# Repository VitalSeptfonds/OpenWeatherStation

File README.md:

# OpenWeatherStation

## The Project
The main goal is to create an Open Weather Station based on STM32.
This weather station will give access to real time data through an Web API.

### Main Functionality 
- POE : Power Over Ethernet
- 3D printable 
- Ingress Protection : IP33
  - Protected from tools and wires greater than 2.5 millimeters
  - Protected from water spray less than 60 degrees from vertical
- Real time data
- Sensors :
  - Temperature
  - Humidity
  - Pressure
  - Light

## API
### Request
`GET /get_data/`

Return Real Time Data

### Response

    {
      "time" : "01/01/01 00:00:00",
      "data" :
        {
          "temperature" : 20.00,
          "humidity" : 50,
          "pressure" : 1013,
          "light" : 3000
        }

    }

## Error handling

Error responses should include a common HTTP status code, message for the developer, message for the end-user (when appropriate), internal error code

    {
      "error" :
        {
          "status" : 400,
          "errorCode" : "444444",
          "errorMessage" : "Verbose, plain language description of the problem. Provide developers
           suggestions about how to solve their problems here",
          "userMessage" : "This is a message that can be passed along to end-users, if needed."
         }
    }

Use three simple, common response codes :

* 400 - Bad Request
* 404 - Not Found
* 500 - Internal Server Error

## Links
* [Hardware](hardware/readme.md)
* [Software](software/readme.md)

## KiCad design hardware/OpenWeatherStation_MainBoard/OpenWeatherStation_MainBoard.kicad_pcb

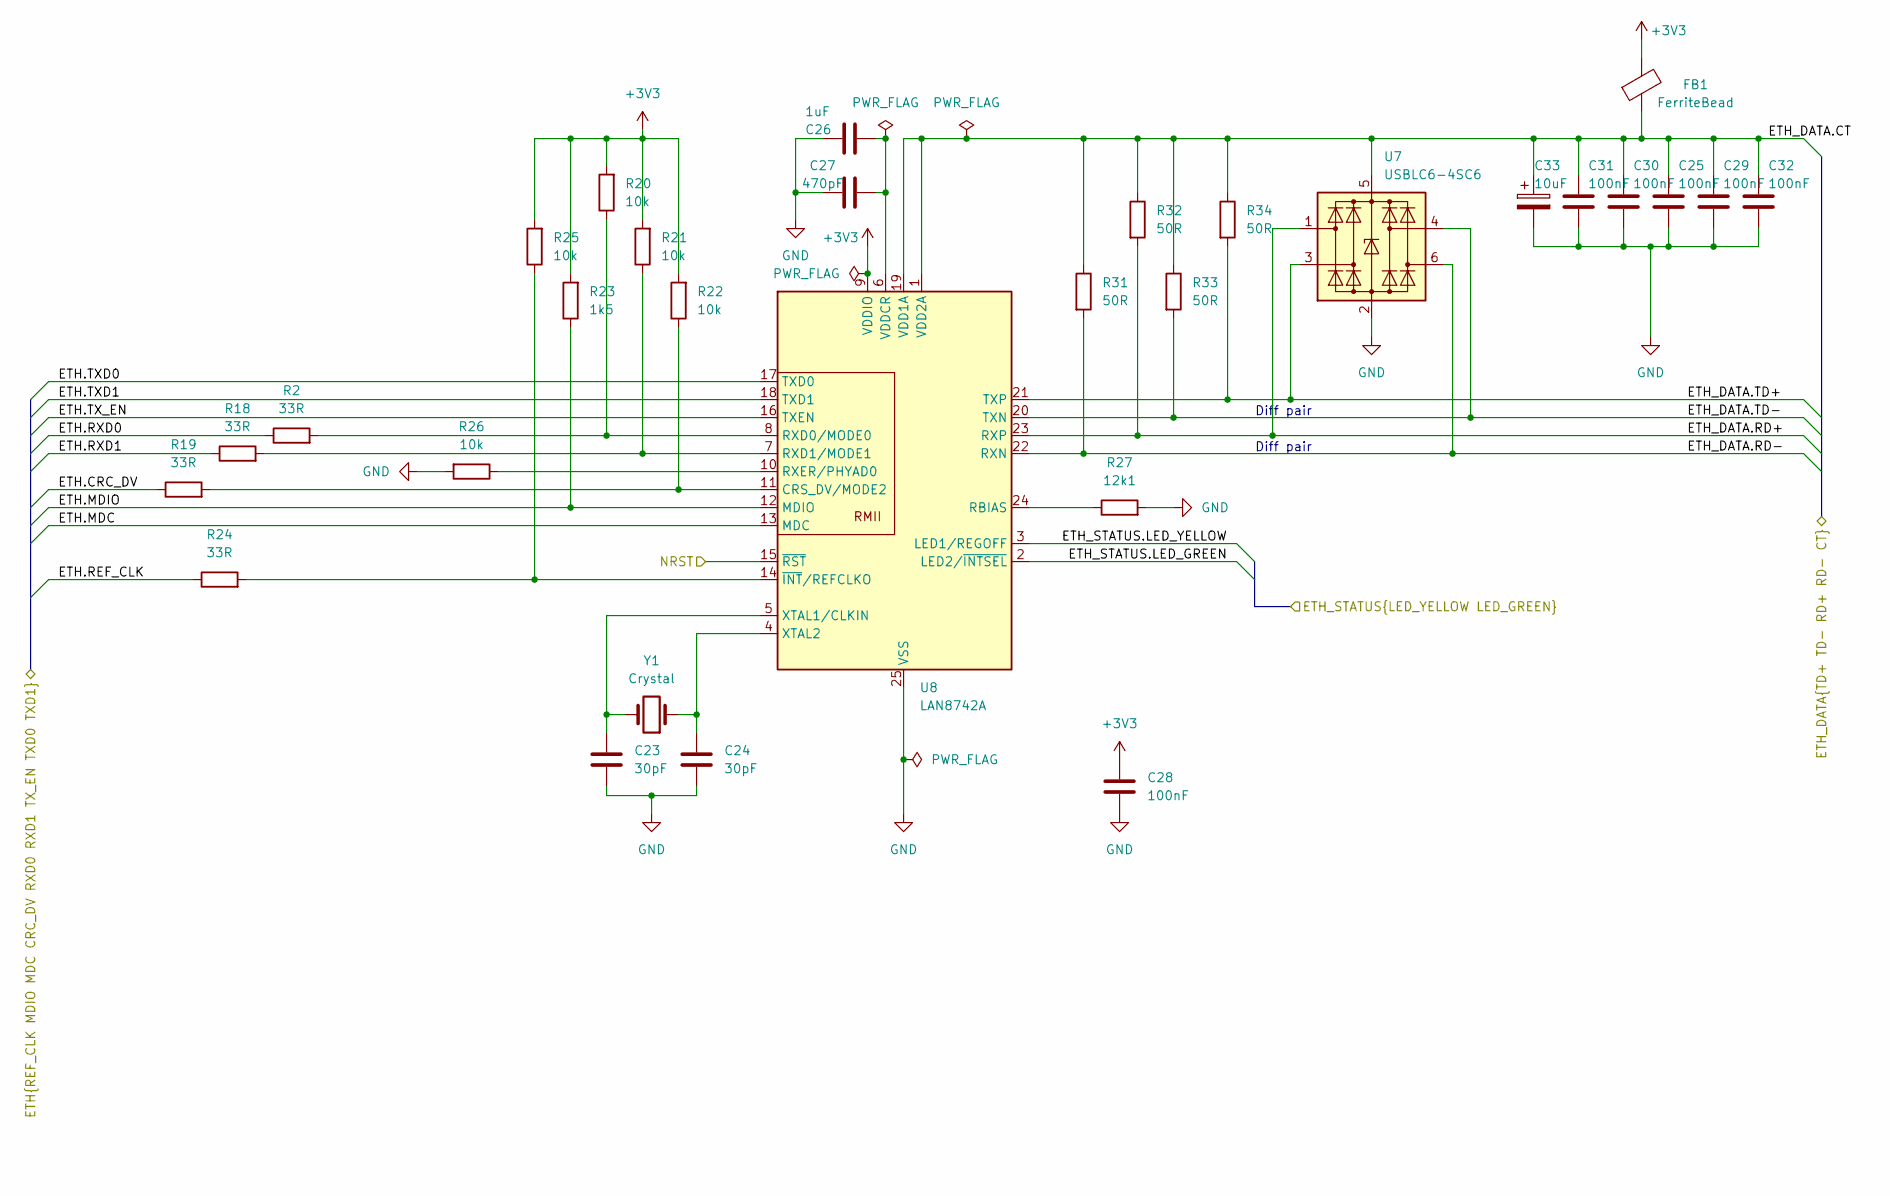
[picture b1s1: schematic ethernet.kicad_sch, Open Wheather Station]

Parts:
C23, C24: 30pF; C_0603_1608Metric
C25, C28, C29, C30, C31, C32: 100nF; C_0603_1608Metric
C26: 1uF; C_0603_1608Metric
C27: 470pF; C_0603_1608Metric
C33: 10uF; C_0603_1608Metric
FB1: FerriteBead; C_0603_1608Metric
R2, R18, R19, R24: 33R; R_0603_1608Metric
R20, R21, R22, R25, R26: 10k; R_0603_1608Metric
R23: 1k5; R_0603_1608Metric
R27: 12k1; R_0603_1608Metric
R31, R32, R33, R34: 50R; R_0603_1608Metric
U7: USBLC6-4SC6; SOT-23-6
U8: LAN8742A; VQFN-24-1EP_4x4mm_P0.5mm_EP2.5x2.5mm_ThermalVias
Y1: Crystal; Crystal_SMD_Abracon_ABM3B-4Pin_5.0x3.2mm

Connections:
+3V3: C28.1, FB1.2, R20.2, R21.2, R22.2, R23.2, R25.2, U8.9 (VDDIO); also elsewhere on the board
/Connectors/ETH_STATUS.LED_GREEN: U8.2 (LED2/~INTSEL); also elsewhere on the board
/Connectors/ETH_STATUS.LED_YELLOW: U8.3 (LED1/REGOFF); also elsewhere on the board
/Connectors/NRST: U8.15 (~RST); also elsewhere on the board
/Ethernet/ETH.CRC_DV: R19.1; also elsewhere on the board
/Ethernet/ETH.MDC: U8.13 (MDC); also elsewhere on the board
/Ethernet/ETH.MDIO: R23.1, U8.12 (MDIO); also elsewhere on the board
/Ethernet/ETH.REF_CLK: R24.1; also elsewhere on the board
/Ethernet/ETH.RXD0: R2.1; also elsewhere on the board
/Ethernet/ETH.RXD1: R18.1; also elsewhere on the board
/Ethernet/ETH.TXD0: U8.17 (TXD0); also elsewhere on the board
/Ethernet/ETH.TXD1: U8.18 (TXD1); also elsewhere on the board
/Ethernet/ETH.TX_EN: U8.16 (TXEN); also elsewhere on the board
/Ethernet/ETH_DATA.CT: C25.1, C29.1, C30.1, C31.1, C32.1, C33.1, FB1.1, R31.1, R32.1, R33.1, R34.1, U7.5 (VBUS), U8.1 (VDD2A), U8.19 (VDD1A); also elsewhere on the board
/Ethernet/ETH_DATA.RD+: R32.2, U7.1 (I/O1), U8.23 (RXP); also elsewhere on the board
/Ethernet/ETH_DATA.RD-: R31.2, U7.6 (I/O4), U8.22 (RXN); also elsewhere on the board
/Ethernet/ETH_DATA.TD+: R34.2, U7.3 (I/O2), U8.21 (TXP); also elsewhere on the board
/Ethernet/ETH_DATA.TD-: R33.2, U7.4 (I/O3), U8.20 (TXN); also elsewhere on the board
GND: C23.2, C24.2, C25.2, C26.2, C27.1, C28.2, C29.2, C30.2, C31.2, C32.2, C33.2, R26.2, R27.2, U7.2 (GND), U8.25 (VSS); also elsewhere on the board
unnamed: R19.2, R22.1, U8.11 (CRS_DV/MODE2)
unnamed: R27.1, U8.24 (RBIAS)
unnamed: R2.2, R20.1, U8.8 (RXD0/MODE0)
unnamed: R18.2, R21.1, U8.7 (RXD1/MODE1)
unnamed: R26.1, U8.10 (RXER/PHYAD0)
unnamed: C26.1, C27.2, U8.6 (VDDCR)
unnamed: C23.1, U8.5 (XTAL1/CLKIN), Y1.2
unnamed: C24.1, U8.4 (XTAL2), Y1.1
unnamed: R24.2, R25.1, U8.14 (~INT/REFCLKO)

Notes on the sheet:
Diff pair

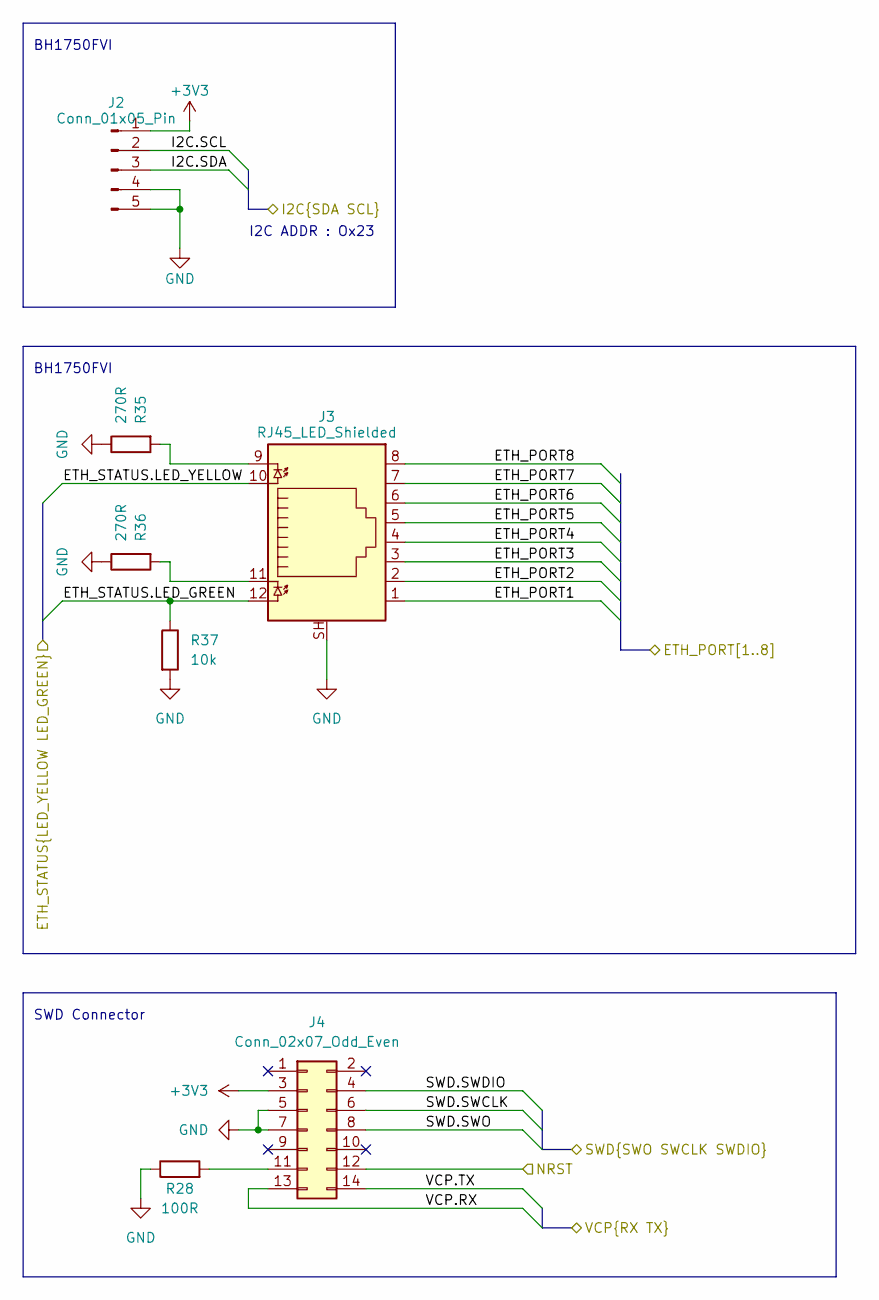
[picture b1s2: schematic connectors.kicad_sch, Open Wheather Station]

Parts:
J2: Conn_01x05_Pin; JST_XH_B5B-XH-A_1x05_P2.50mm_Vertical
J3: RJ45_LED_Shielded; RJ45_Amphenol_RJHSE538X
J4: Conn_02x07_Odd_Even; PinHeader_2x07_P1.27mm_Vertical
R28: 100R; R_0603_1608Metric
R35, R36: 270R; R_0603_1608Metric
R37: 10k; R_0603_1608Metric

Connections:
+3V3: J2.1, J4.3; also elsewhere on the board
/Connectors/ETH_PORT1: J3.1; also elsewhere on the board
/Connectors/ETH_PORT2: J3.2; also elsewhere on the board
/Connectors/ETH_PORT3: J3.3; also elsewhere on the board
/Connectors/ETH_PORT4: J3.4; also elsewhere on the board
/Connectors/ETH_PORT5: J3.5; also elsewhere on the board
/Connectors/ETH_PORT6: J3.6; also elsewhere on the board
/Connectors/ETH_PORT7: J3.7; also elsewhere on the board
/Connectors/ETH_PORT8: J3.8; also elsewhere on the board
/Connectors/ETH_STATUS.LED_GREEN: J3.12, R37.1; also elsewhere on the board
/Connectors/ETH_STATUS.LED_YELLOW: J3.10; also elsewhere on the board
/Connectors/I2C.SCL: J2.2; also elsewhere on the board
/Connectors/I2C.SDA: J2.3; also elsewhere on the board
/Connectors/NRST: J4.12; also elsewhere on the board
/Connectors/SWD.SWCLK: J4.6; also elsewhere on the board
/Connectors/SWD.SWDIO: J4.4; also elsewhere on the board
/Connectors/SWD.SWO: J4.8; also elsewhere on the board
/Connectors/VCP.RX: J4.13; also elsewhere on the board
/Connectors/VCP.TX: J4.14; also elsewhere on the board
GND: J2.4, J2.5, J3.SH, J4.5, J4.7, R28.1, R35.1, R36.1, R37.2; also elsewhere on the board
unnamed: J3.9, R35.2
unnamed: J3.11, R36.2
unnamed: J4.11, R28.2

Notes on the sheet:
SWD Connector
I2C ADDR : Ox23
BH1750FVI

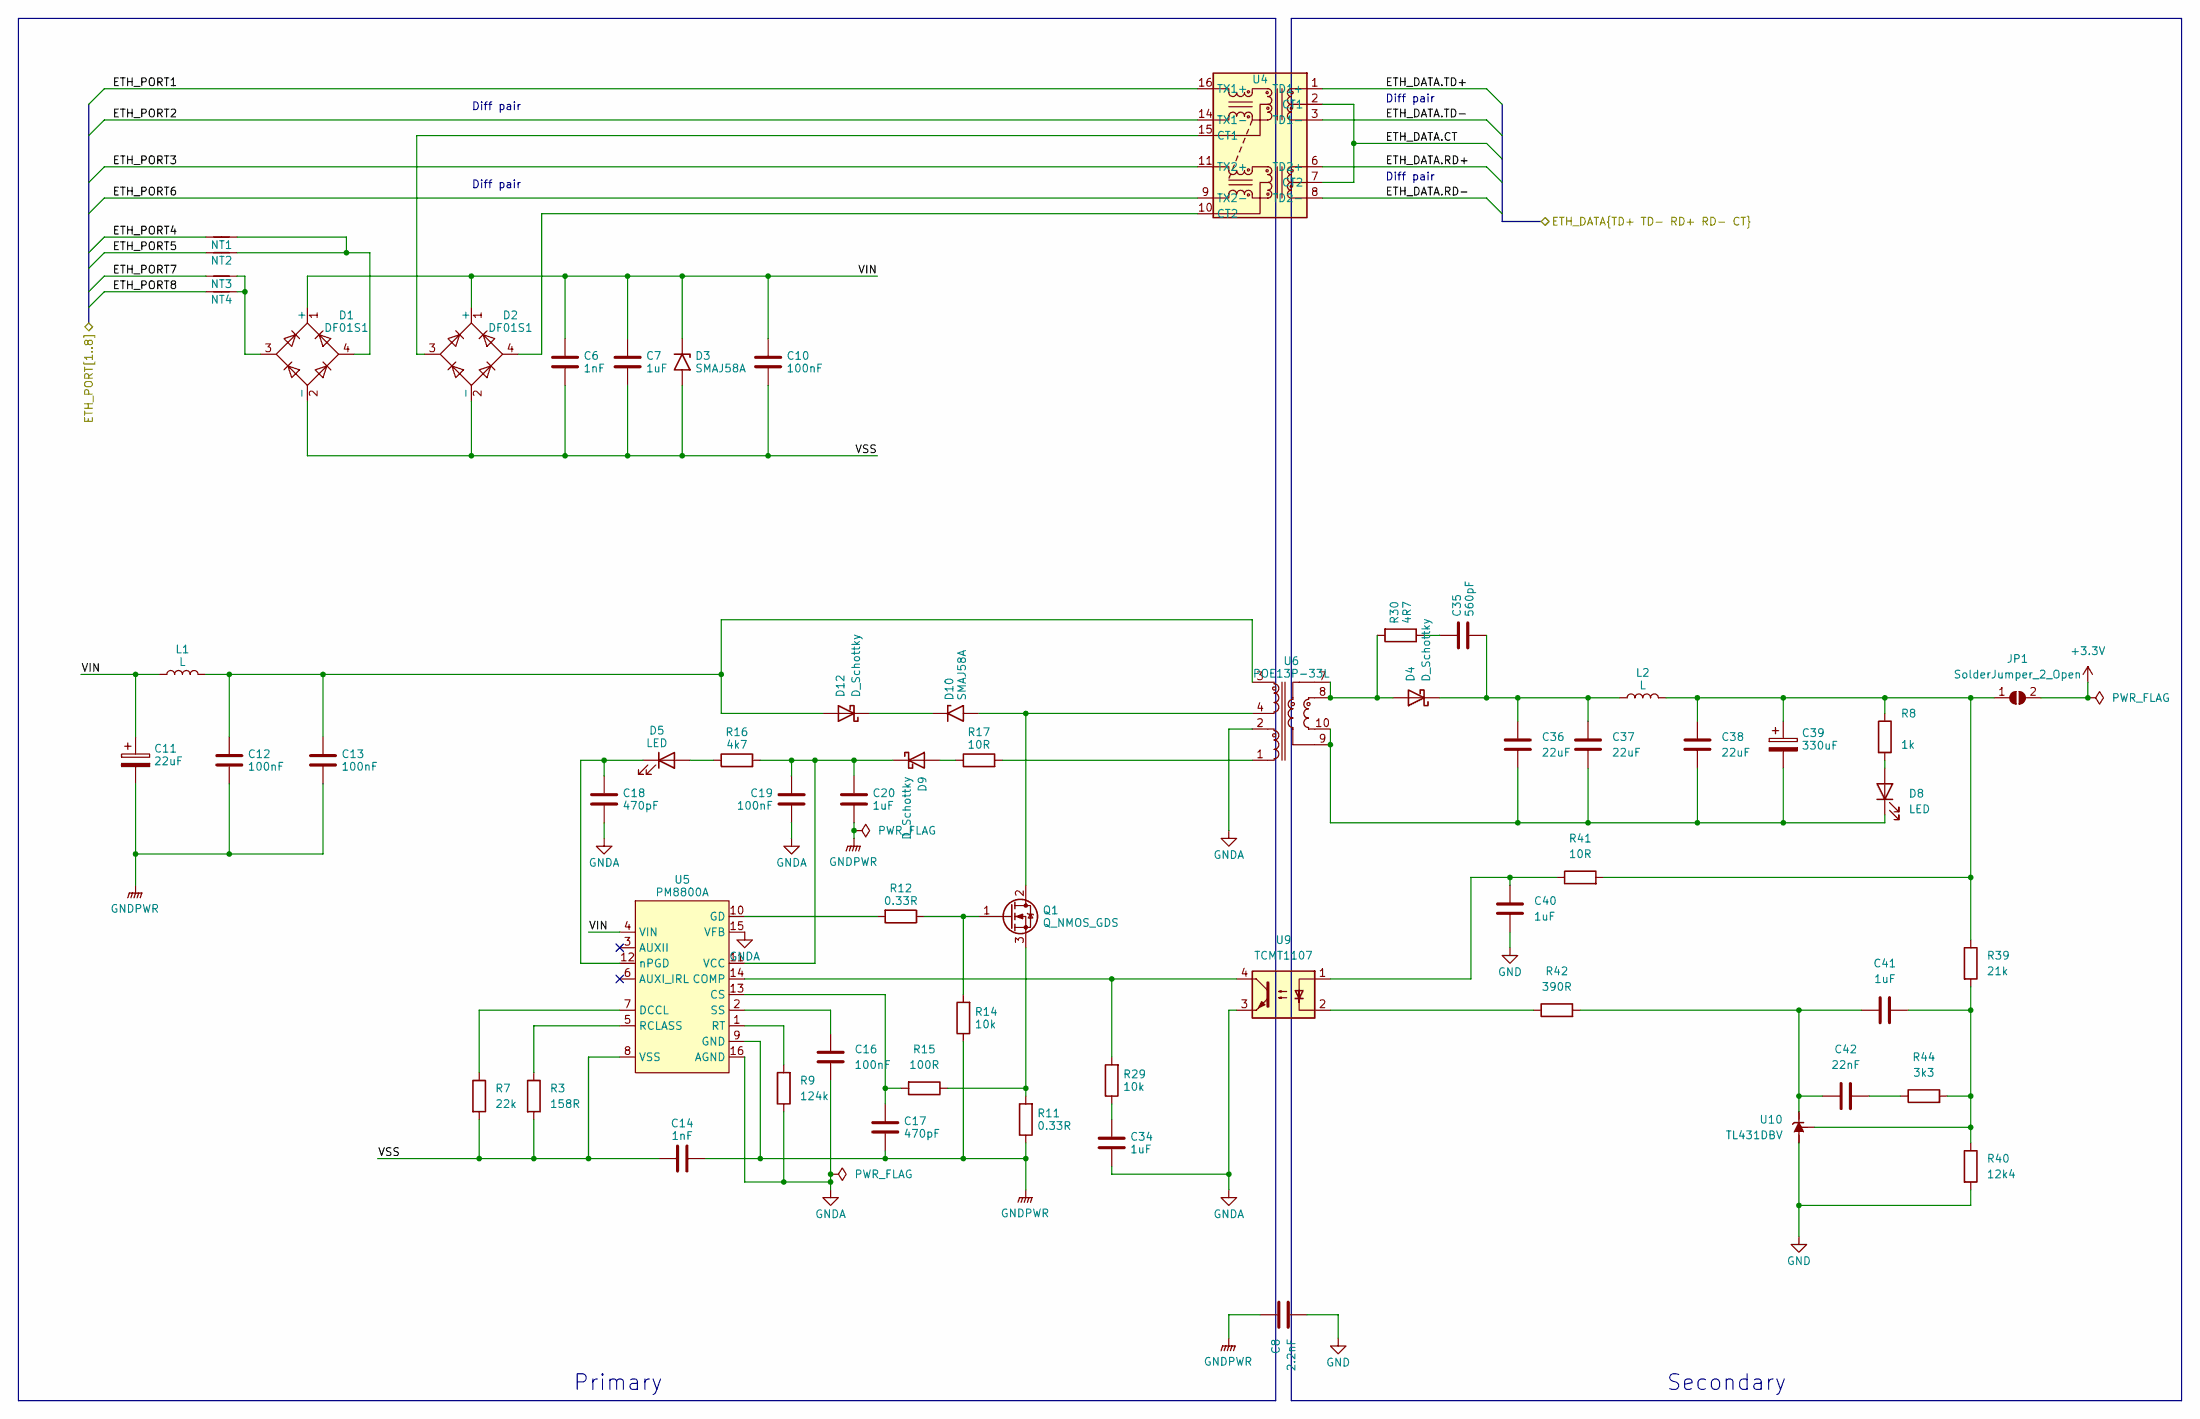
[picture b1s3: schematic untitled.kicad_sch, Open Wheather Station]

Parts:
C6, C14: 1nF; C_0603_1608Metric
C7, C20, C34, C40, C41: 1uF; C_0603_1608Metric
C8: 2.2nF; C_0603_1608Metric
C10, C12, C13, C16, C19: 100nF; C_0603_1608Metric
C11: 22uF; CP_Elec_5x3
C17, C18: 470pF; C_0603_1608Metric
C35: 560pF; C_0603_1608Metric
C36, C37, C38: 22uF; C_0603_1608Metric
C39: 330uF; CP_Elec_5x3
C42: 22nF; C_0603_1608Metric
D1, D2: DF01S1; Diode_Bridge_OnSemi_SDIP-4L
D3, D10: SMAJ58A; D_SMA
D4: D_Schottky; D_PowerDI-5
D5, D8: LED; LED_D3.0mm
D9, D12: D_Schottky; D_1206_3216Metric
JP1: SolderJumper_2_Open; SolderJumper-2_P1.3mm_Open_RoundedPad1.0x1.5mm
L1, L2: L; L_1206_3216Metric
NT1, NT2, NT3, NT4: NetTie_2; NetTie-2_SMD_Pad0.5mm
Q1: Q_NMOS_GDS; TO-252-2
R3: 158R; R_0603_1608Metric
R7: 22k; R_0603_1608Metric
R8: 1k; R_0603_1608Metric
R9: 124k; R_0603_1608Metric
R11: 0.33R; R_1206_3216Metric
R12: 0.33R; R_0603_1608Metric
R14, R29: 10k; R_0603_1608Metric
R15: 100R; R_0603_1608Metric
R16: 4k7; R_0603_1608Metric
R17, R41: 10R; R_0603_1608Metric
R30: 4R7; R_0603_1608Metric
R39: 21k; R_0603_1608Metric
R40: 12k4; R_0603_1608Metric
R42: 390R; R_0603_1608Metric
R44: 3k3; R_0603_1608Metric
U4: Transformer_Ethernet_Wuerth_749013011A
U5: PM8800A; HTSSOP-16-1EP_4.4x5mm_P0.65mm_EP3x3mm
U6: POE13P-33L; SM13117EL
U9: TCMT1107; SOP-4_4.4x2.6mm_P1.27mm
U10: TL431DBV; SOT-23-5

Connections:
+3.3V: JP1.2 (B)
/Connectors/ETH_PORT1: U4.16 (TX1+); also elsewhere on the board
/Connectors/ETH_PORT2: U4.14 (TX1-); also elsewhere on the board
/Connectors/ETH_PORT3: U4.11 (TX2+); also elsewhere on the board
/Connectors/ETH_PORT4: NT1.1; also elsewhere on the board
/Connectors/ETH_PORT5: NT2.1; also elsewhere on the board
/Connectors/ETH_PORT6: U4.9 (TX2-); also elsewhere on the board
/Connectors/ETH_PORT7: NT3.1; also elsewhere on the board
/Connectors/ETH_PORT8: NT4.1; also elsewhere on the board
/Ethernet/ETH_DATA.CT: U4.2 (CT1), U4.7 (CT2); also elsewhere on the board
/Ethernet/ETH_DATA.RD+: U4.6 (TD2+); also elsewhere on the board
/Ethernet/ETH_DATA.RD-: U4.8 (TD2-); also elsewhere on the board
/Ethernet/ETH_DATA.TD+: U4.1 (TD1+); also elsewhere on the board
/Ethernet/ETH_DATA.TD-: U4.3 (TD1-); also elsewhere on the board
/PoE/VIN: C6.1, C7.1, C10.1, C11.1, D1.1 (+), D2.1 (+), D3.1 (A1), L1.1, U5.4 (VIN)
/PoE/VSS: C6.2, C7.2, C10.2, C14.1, D1.2 (-), D2.2 (-), D3.2 (A2), R3.2, R7.2, U5.8 (VSS)
GND: C8.2, C40.1, R40.2, U10.5 (A); also elsewhere on the board
GNDA: C16.2, C18.2, C19.2, C34.2, R9.1, U5.15 (VFB), U5.16 (AGND), U6.2, U9.3
GNDPWR: C8.1, C11.2, C12.2, C13.2, C14.2, C17.2, C20.2, R11.1, R14.1, U5.9 (GND)
unnamed: C34.1, R29.1
unnamed: C35.1, R30.1
unnamed: C40.2, R41.1, U9.1
unnamed: C42.1, R44.1
unnamed: D1.3, NT3.2, NT4.2
unnamed: D1.4, NT1.2, NT2.2
unnamed: D2.3, U4.15 (CT1)
unnamed: D2.4, U4.10 (CT2)
unnamed: D4.2 (A), R30.2, U6.7, U6.8
unnamed: C35.2, C36.2, C37.2, D4.1 (K), L2.1
unnamed: D5.2 (A), R16.1
unnamed: C18.1, D5.1 (K), U5.12 (nPGD)
unnamed: D8.2 (A), R8.2
unnamed: C36.1, C37.1, C38.1, C39.2, D8.1 (K), U6.9, U6.10
unnamed: D9.2 (A), R17.1
unnamed: C19.1, C20.1, D9.1 (K), R16.2, U5.11 (VCC)
unnamed: D10.1 (A1), D12.1 (K)
unnamed: D10.2 (A2), Q1.2 (D), U6.4
unnamed: C12.1, C13.1, D12.2 (A), L1.2, U6.3
unnamed: C38.2, C39.1, JP1.1 (A), L2.2, R8.1, R39.1, R41.2
unnamed: Q1.1 (G), R12.1, R14.2
unnamed: Q1.3 (S), R11.2, R15.1
unnamed: R17.2, U6.1
unnamed: R42.1, U9.2
unnamed: R29.2, U5.14 (COMP), U9.4
unnamed: C17.1, R15.2, U5.13 (CS)
unnamed: R7.1, U5.7 (DCCL)
unnamed: R12.2, U5.10 (GD)
unnamed: R3.1, U5.5 (RCLASS)
unnamed: R9.2, U5.1 (RT)
unnamed: C16.1, U5.2 (SS)
unnamed: C41.2, C42.2, R42.2, U10.3 (K)
unnamed: C41.1, R39.2, R40.1, R44.2, U10.4 (REF)

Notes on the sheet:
Diff pair
Secondary
Primary

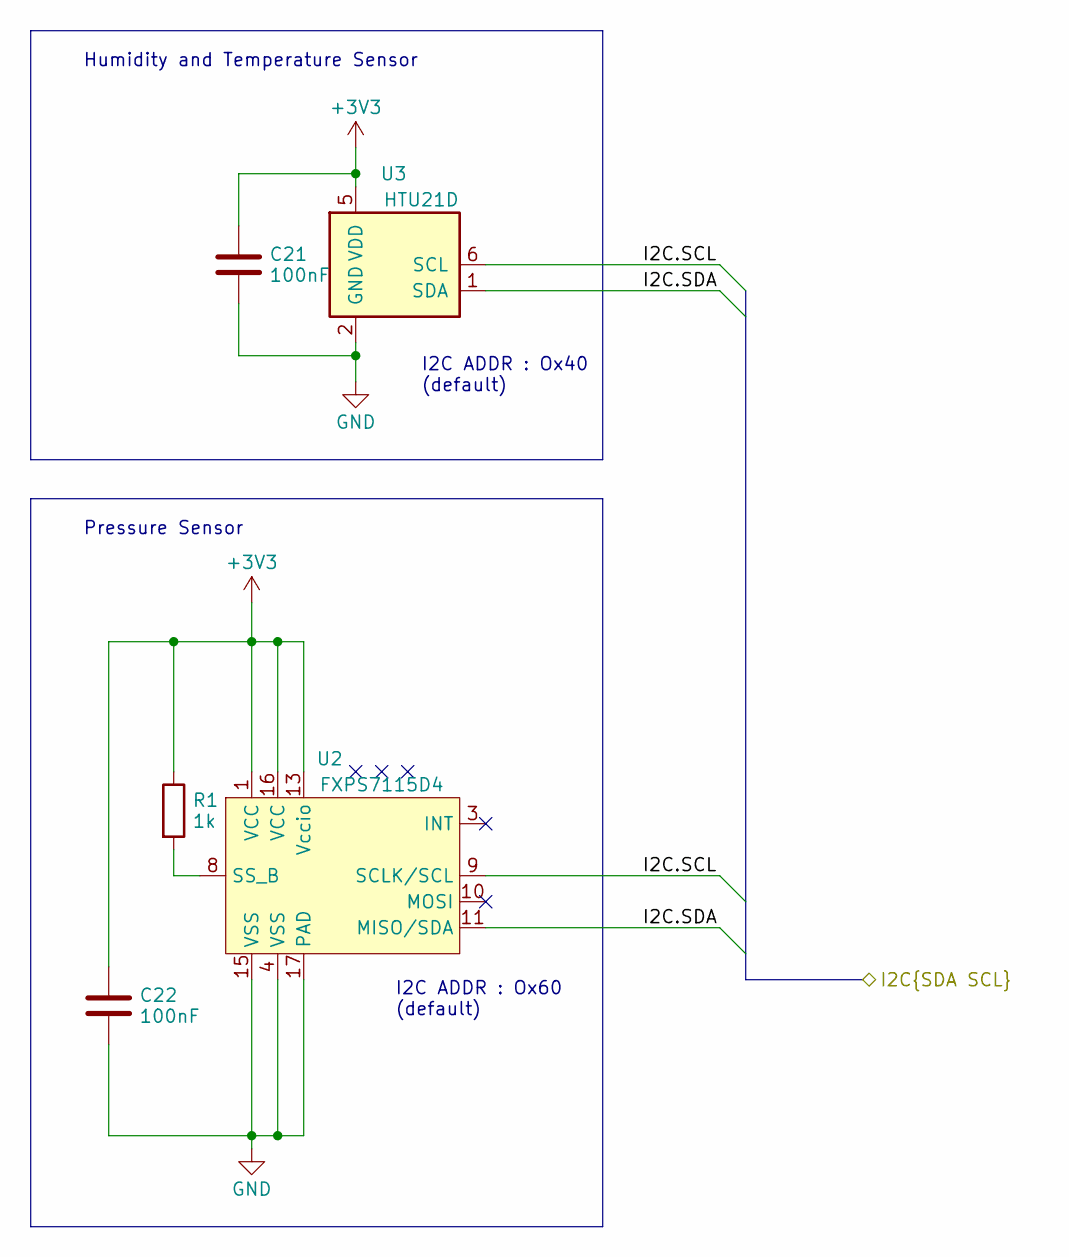
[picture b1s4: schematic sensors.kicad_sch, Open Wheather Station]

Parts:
C21, C22: 100nF; C_0603_1608Metric
R1: 1k; R_0603_1608Metric
U2: FXPS7115D4; Panasonic_HQFN-16-1EP_4x4mm_P0.65mm_EP2.9x2.9mm
U3: HTU21D; DFN-6-1EP_3x3mm_P1mm_EP1.5x2.4mm

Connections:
+3V3: C21.1, C22.1, R1.1, U2.1 (VCC), U2.13 (Vccio), U2.16 (VCC), U3.5 (VDD); also elsewhere on the board
/Connectors/I2C.SCL: U2.9 (SCLK/SCL), U3.6 (SCL); also elsewhere on the board
/Connectors/I2C.SDA: U2.11 (MISO/SDA), U3.1 (SDA); also elsewhere on the board
GND: C21.2, C22.2, U2.4 (VSS), U2.15 (VSS), U2.17 (PAD), U3.2 (GND); also elsewhere on the board
unnamed: R1.2, U2.8 (SS_B)

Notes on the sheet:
I2C ADDR : Ox60 (default)
I2C ADDR : Ox40 (default)
Pressure Sensor
Humidity and Temperature Sensor

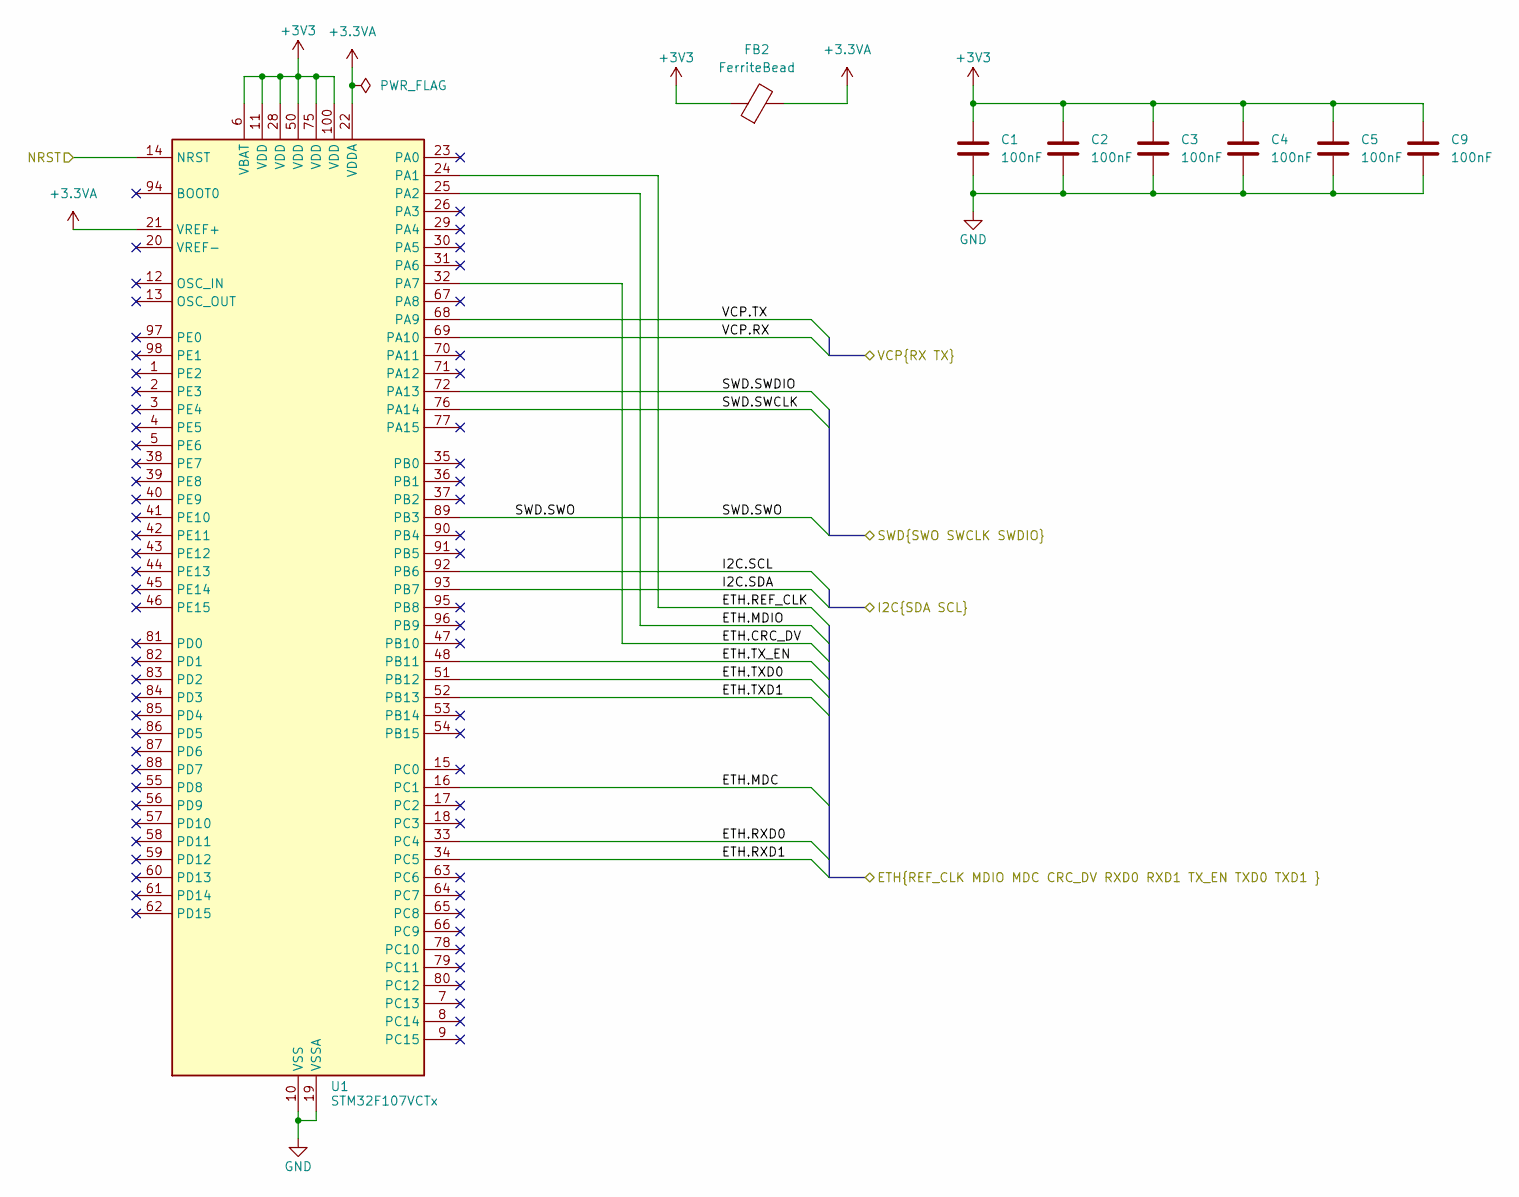
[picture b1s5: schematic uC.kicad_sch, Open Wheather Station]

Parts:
C1, C2, C3, C4, C5, C9: 100nF; C_0603_1608Metric
FB2: FerriteBead; C_0603_1608Metric
U1: STM32F107VCTx; LQFP-100_14x14mm_P0.5mm

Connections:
+3.3VA: FB2.2, U1.21 (VREF+), U1.22 (VDDA)
+3V3: C1.1, C2.1, C3.1, C4.1, C5.1, C9.1, FB2.1, U1.6 (VBAT), U1.11 (VDD), U1.28 (VDD), U1.50 (VDD), U1.75 (VDD), U1.100 (VDD); also elsewhere on the board
/Connectors/I2C.SCL: U1.92 (PB6); also elsewhere on the board
/Connectors/I2C.SDA: U1.93 (PB7); also elsewhere on the board
/Connectors/NRST: U1.14 (NRST); also elsewhere on the board
/Connectors/SWD.SWCLK: U1.76 (PA14); also elsewhere on the board
/Connectors/SWD.SWDIO: U1.72 (PA13); also elsewhere on the board
/Connectors/SWD.SWO: U1.89 (PB3); also elsewhere on the board
/Connectors/VCP.RX: U1.69 (PA10); also elsewhere on the board
/Connectors/VCP.TX: U1.68 (PA9); also elsewhere on the board
/Ethernet/ETH.CRC_DV: U1.32 (PA7); also elsewhere on the board
/Ethernet/ETH.MDC: U1.16 (PC1); also elsewhere on the board
/Ethernet/ETH.MDIO: U1.25 (PA2); also elsewhere on the board
/Ethernet/ETH.REF_CLK: U1.24 (PA1); also elsewhere on the board
/Ethernet/ETH.RXD0: U1.33 (PC4); also elsewhere on the board
/Ethernet/ETH.RXD1: U1.34 (PC5); also elsewhere on the board
/Ethernet/ETH.TXD0: U1.51 (PB12); also elsewhere on the board
/Ethernet/ETH.TXD1: U1.52 (PB13); also elsewhere on the board
/Ethernet/ETH.TX_EN: U1.48 (PB11); also elsewhere on the board
GND: C1.2, C2.2, C3.2, C4.2, C5.2, C9.2, U1.10 (VSS), U1.19 (VSSA), U1.27 (VSS), U1.49 (VSS), U1.74 (VSS), U1.99 (VSS); also elsewhere on the board

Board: 2 copper layers, 111 parts (33 on the bottom side), 85 nets, no tracks yet.

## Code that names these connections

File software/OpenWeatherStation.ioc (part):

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Mcu.Name=STM32F107R(B-C)Tx
Mcu.Package=LQFP64
Mcu.UserName=STM32F107RCTx
PA1.Mode=RMII
PA1.Signal=ETH_REF_CLK
PA10.Mode=Asynchronous
PA10.Signal=USART1_RX
PA13.Mode=Trace_Asynchronous_SW
PA13.Signal=SYS_JTMS-SWDIO
PA14.Mode=Trace_Asynchronous_SW
PA14.Signal=SYS_JTCK-SWCLK
PA2.Mode=RMII
PA2.Signal=ETH_MDIO
PA7.Mode=RMII
PA7.Signal=ETH_CRS_DV
PA9.Mode=Asynchronous
PA9.Signal=USART1_TX
PB11.Mode=RMII
PB11.Signal=ETH_TX_EN
PB12.Mode=RMII
PB12.Signal=ETH_TXD0
PB13.Mode=RMII
PB13.Signal=ETH_TXD1
PB3.Mode=Trace_Asynchronous_SW
PB3.Signal=SYS_TRACESWO
PB6.Mode=I2C
PB6.Signal=I2C1_SCL
PB7.Mode=I2C
PB7.Signal=I2C1_SDA
PC1.Mode=RMII
PC1.Signal=ETH_MDC
PC4.Mode=RMII
PC4.Signal=ETH_RXD0
PC5.Mode=RMII
PC5.Signal=ETH_RXD1
RCC.SYSCLKFreq_VALUE=36000000
RCC.SYSCLKSource=RCC_SYSCLKSOURCE_PLLCLK
board=custom

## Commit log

2021-09-14 add datasheet
2021-09-14 clean
2021-09-14 add kicad project
2021-09-14 add stm32 project
2021-09-14 Rename hardware.md to readme.md
2021-09-14 add casing catia main assembly file
2021-09-18 Update issue templates
2021-09-18 Create LICENSE
2021-09-18 CAD : add light sensor and main part of the casing
2021-09-18 design main case, work in progress
2021-09-18 add cad rendering
2021-09-21 fix name issue
2021-10-03 minor
2022-01-28 update mechanical design
2022-01-28 add production setup and files for casing
2022-01-29 update main part design
2022-01-29 improve Water resistance of casing
2022-01-29 update casing, add wall support ,update production setup
2022-02-01 adjust hole size and stl mesh size, new production files
2022-02-03 fix screew lenght
2022-03-27 update doc and schematic
2022-10-24 update schematic
2023-06-18 electronic design wip : sensors and connectors : done
2023-06-19 poe design wip
2023-12-31 add datasheets
2023-12-31 update board schematics (sensors, ethernet ...)
2023-12-31 update project version
2023-12-31 update stm32 cube ide version
2023-12-31 fix hierarchical bus
2023-12-31 elec save
2023-12-31 update pcb kicad version
2023-12-31 Create nucleo f676.pdf
    add nucleo board schematic for ethernet implementation example
2023-12-31 move eth connector to dedicated sheet
2024-01-01 poe wip
2024-01-01 add stm doc and stlink
2024-01-01 update schematics
2024-01-01 add swd with trace and uart comm
2024-01-01 schematic update
2024-01-01 minor schematic update
2024-01-01 Delete an4415-power-over-ethernetpd-converter-with-33-v-3-a-output-standard-ieee-8023af-compliant-stmicroelectronics (1).pdf
    rm doc duplicate
2024-01-01 electrical design wip
2024-01-02 update elec
2024-01-02 udpate pcb design
2024-01-02 update pcb
2024-01-02 modif 3d casing
2024-01-02 update 3d
